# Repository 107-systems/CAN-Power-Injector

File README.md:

`CAN-Power-Injector`
====================

The purpose of this board is to inject 5V DC power at up to 5A for powering CAN bus devices.

<p align="center">
  
</p>

#### Blockdiagram

#### Electrical Parameters
| Name | Value |
|-|-|
| V_IN min | 10.5 V | set by resistor divider(R7/R8) |
| V_IN max | 40.0 V | limited by TVS diode (D4) |
| V_CAN_OUT | 5.0 V to 5.5 V|
| I_CAN_OUT,CONTINUOUS | 5.0 A |

#### Inputs
| Designator | Name | Connector |
|-|-|-|
| CN4 | Battery (4S / 4100 mAh LiFePo) | [Powerpole® PP15 to PP45](https://www.andersonpower.com/content/dam/app/ecommerce/product-pdfs/PP-Pak/ds-pp1545.pdf) |
| CN1 | Battery | 3.5 mm screw terminal (not populated) |

#### Outputs
| Designator | Name | Connector |
|-|-|-|
| CN2 and CN3 | CAN channel 1 | JST GH 1.25mm 4-pin. |
| CN5 and CN6 | CAN channel 2 | JST GH 1.25mm 4-pin. |
| CN7 | 5V | 5V output, internal for testing (not populated) |

## Enclosure

There exists a 3D printable enclosure to encapsulate the PCB.

### Standard

### Low profile

## PCB
### Top

### Bottom

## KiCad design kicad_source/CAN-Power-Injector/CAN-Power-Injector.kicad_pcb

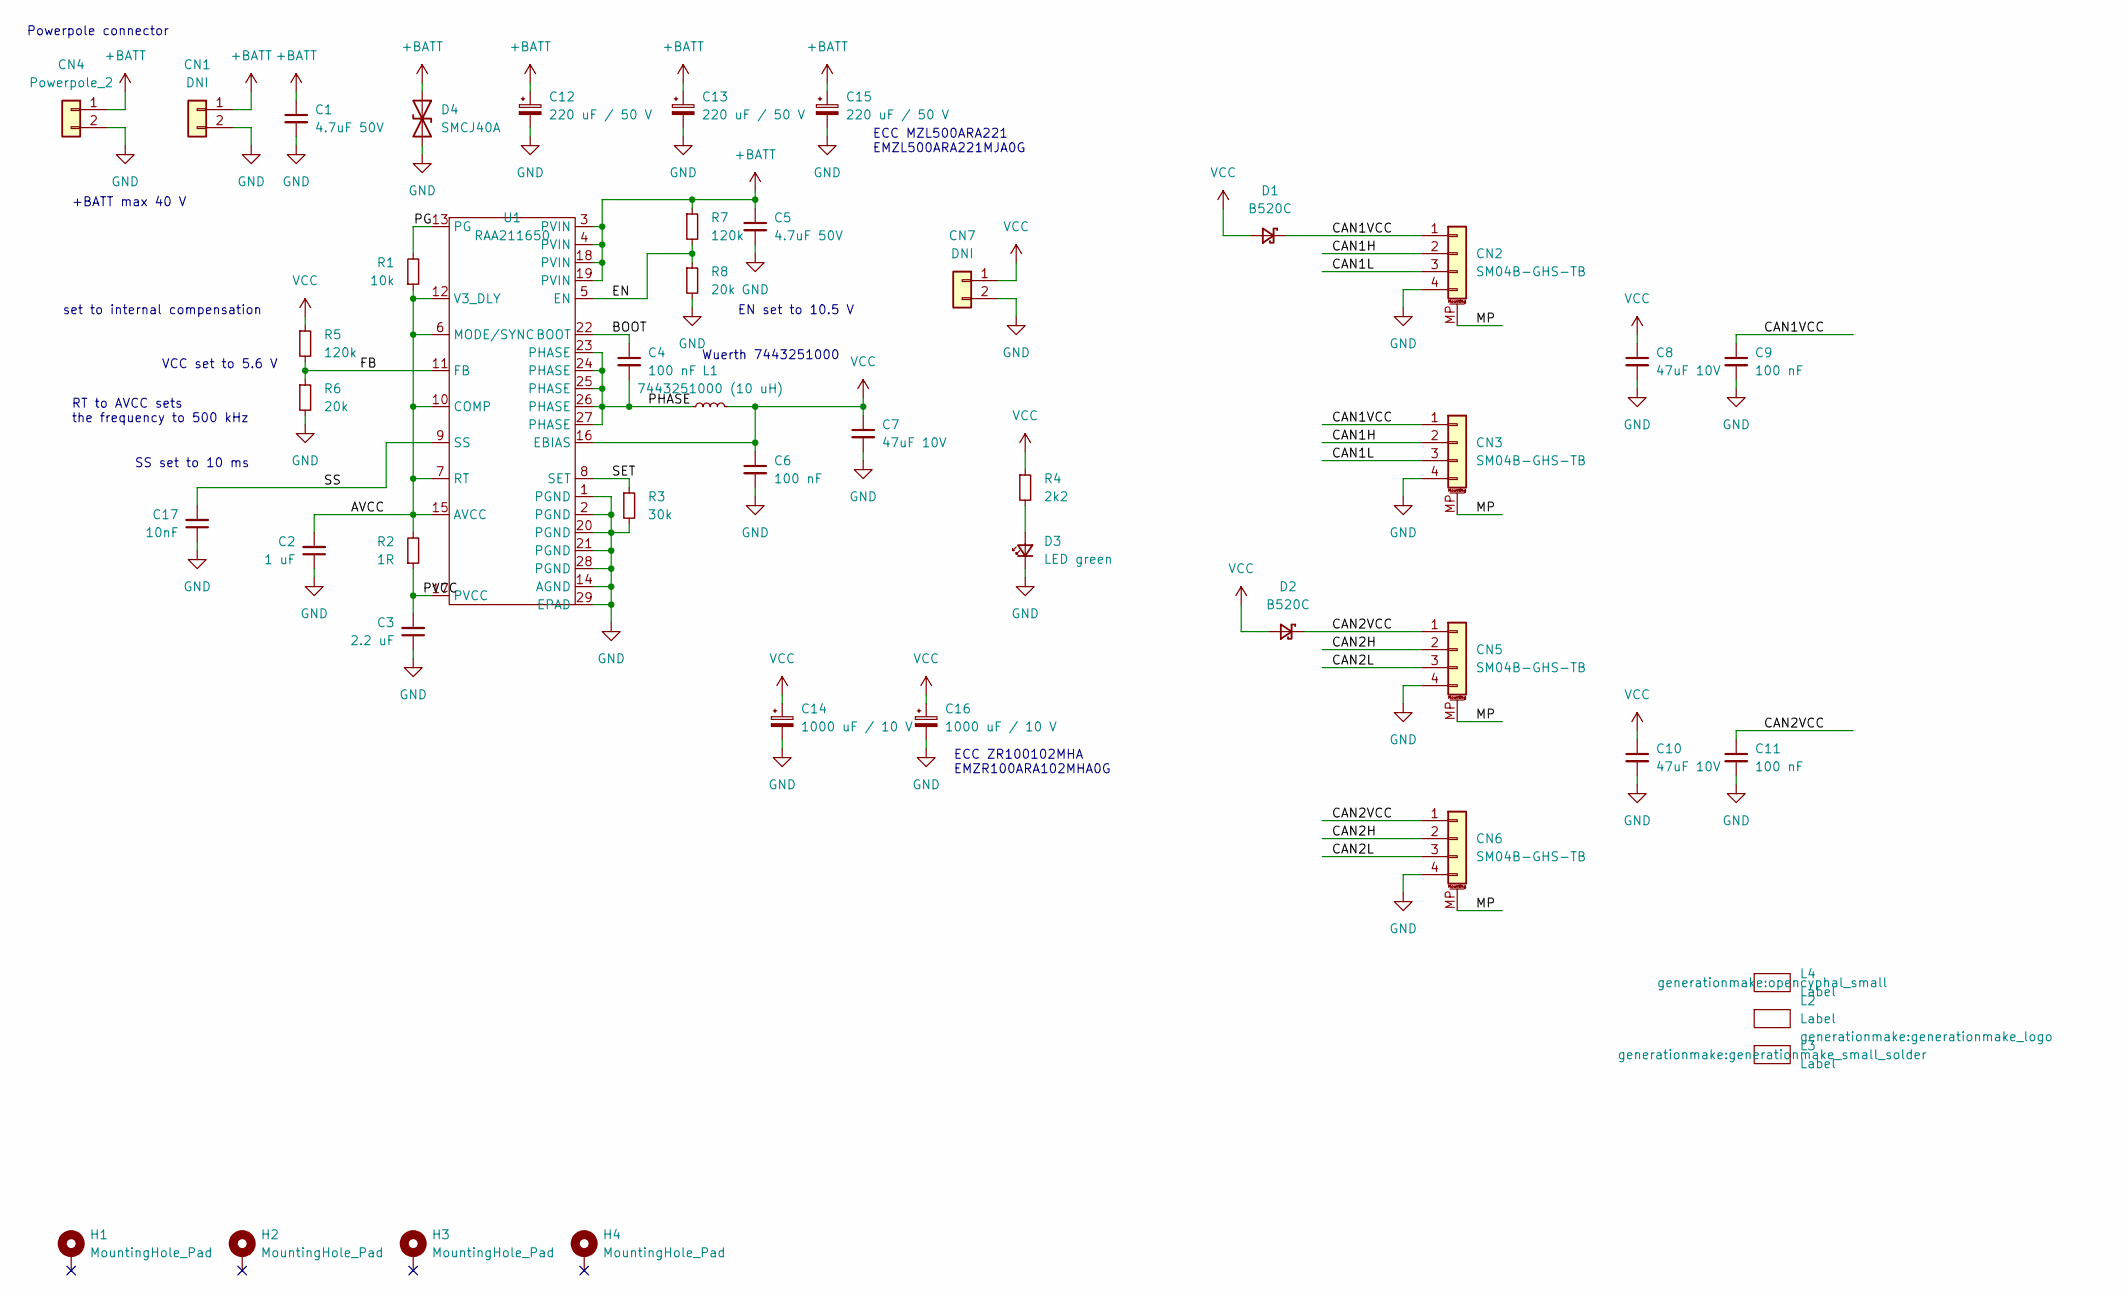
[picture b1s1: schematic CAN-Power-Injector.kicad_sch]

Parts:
C1, C5: 4.7uF 50V; C_1210_3225Metric
C2: 1 uF; C_0603_1608Metric
C3: 2.2 uF; C_0603_1608Metric
C4, C6, C9, C11: 100 nF; C_0603_1608Metric
C7, C8, C10: 47uF 10V; C_1210_3225Metric
C12, C13, C15: 220 uF / 50 V; CP_Elec_10x10
C14, C16: 1000 uF / 10 V; CP_Elec_8x10
C17: 10nF; C_0603_1608Metric
CN1: DNI; PhoenixContact_MC_1,5_2-G-3.5_1x02_P3.50mm_Horizontal
CN2, CN3, CN5, CN6: SM04B-GHS-TB; JST_GH_SM04B-GHS-TB_1x04-1MP_P1.25mm_Horizontal
CN4: Powerpole_2; POWERPOLE_hor_2
CN7: DNI; PinHeader_1x02_P2.54mm_Vertical
D1, D2: B520C; D_SMC
D3: LED green; LED_0603_1608Metric
D4: SMCJ40A; D_SMC
H1, H2, H3, H4: MountingHole_Pad; MountingHole_3.2mm_M3_DIN965_Pad
L1: 7443251000 (10 uH); L_Wuerth_HCI-1050
L2: Label; generationmake_logo
L3: Label; generationmake_small_solder
L4: Label; opencyphal_small
R1: 10k; R_0603_1608Metric
R2: 1R; R_0603_1608Metric
R3: 30k; R_0603_1608Metric
R4: 2k2; R_0603_1608Metric
R5, R7: 120k; R_0603_1608Metric
R6, R8: 20k; R_0603_1608Metric
U1: RAA211650; QFN-28-1EP_4x5mm_P0.5mm_EP2.65x3.65mm

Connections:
+BATT: C1.1, C5.1, C12.1, C13.1, C15.1, CN1.1, CN4.1, D4.1 (A1), R7.1, U1.3 (PVIN), U1.4 (PVIN), U1.18 (PVIN), U1.19 (PVIN)
/AVCC: C2.2, R1.1, R2.2, U1.6 (MODE/SYNC), U1.7 (RT), U1.10 (COMP), U1.12 (V3_DLY), U1.15 (AVCC)
/BOOT: C4.1, U1.22 (BOOT)
/CAN1H: CN2.2, CN3.2
/CAN1L: CN2.3, CN3.3
/CAN1VCC: C9.1, CN2.1, CN3.1, D1.1 (K)
/CAN2H: CN5.2, CN6.2
/CAN2L: CN5.3, CN6.3
/CAN2VCC: C11.1, CN5.1, CN6.1, D2.1 (K)
/EN: R7.2, R8.1, U1.5 (EN)
/FB: R5.2, R6.1, U1.11 (FB)
/MP: CN2.MP (MountPin), CN3.MP (MountPin), CN5.MP (MountPin), CN6.MP (MountPin)
/PG: R1.2, U1.13 (PG)
/PHASE: C4.2, L1.1, U1.23 (PHASE), U1.24 (PHASE), U1.25 (PHASE), U1.26 (PHASE), U1.27 (PHASE)
/PVCC: C3.2, R2.1, U1.17 (PVCC)
/SET: R3.1, U1.8 (SET)
/SS: C17.2, U1.9 (SS)
GND: C1.2, C2.1, C3.1, C5.2, C6.2, C7.2, C8.2, C9.2, C10.2, C11.2, C12.2, C13.2, C14.2, C15.2, C16.2, C17.1, CN1.2, CN2.4, CN3.4, CN4.2, CN5.4, CN6.4, CN7.2, D3.1 (K), D4.2 (A2), R3.2, R6.2, R8.2, U1.1 (PGND), U1.2 (PGND), U1.14 (AGND), U1.20 (PGND), U1.21 (PGND), U1.28 (PGND), U1.29 (EPAD)
unnamed: D3.2 (A), R4.2
VCC: C6.1, C7.1, C8.1, C10.1, C14.1, C16.1, CN7.1, D1.2 (A), D2.2 (A), L1.2, R4.1, R5.1, U1.16 (EBIAS)

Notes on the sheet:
Wuerth 7443251000
EN set to 10.5 V
+BATT max 40 V
ECC ZR100102MHA EMZR100ARA102MHA0G
set to internal compensation
ECC MZL500ARA221 EMZL500ARA221MJA0G
RT to AVCC sets the frequency to 500 kHz
VCC set to 5.6 V
Powerpole connector
SS set to 10 ms

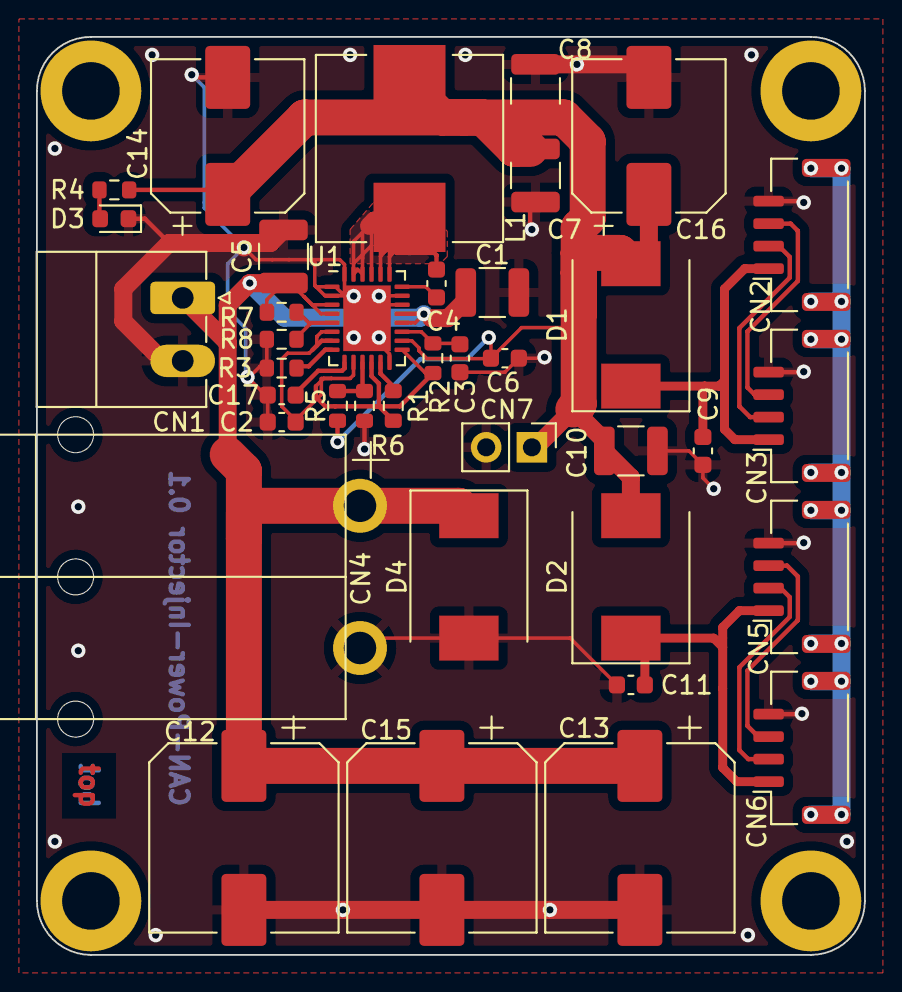
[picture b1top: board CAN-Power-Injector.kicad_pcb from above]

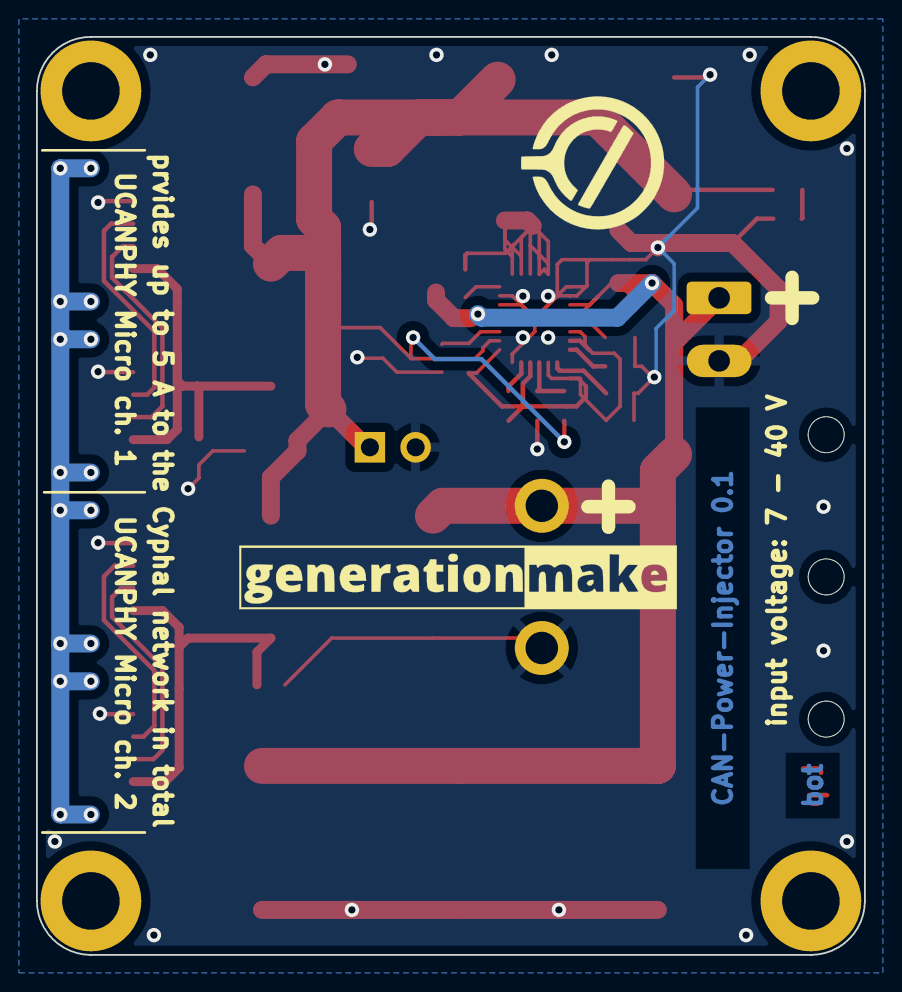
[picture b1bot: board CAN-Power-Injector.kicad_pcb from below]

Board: 2 copper layers, 46.0 x 51.0 mm, 45 parts (2 on the bottom side), 20 nets.

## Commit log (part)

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2022-07-18 Initial commit.
2022-07-18 Fix typo.
2022-07-18 Minimal specification.
2022-08-23 Add l3xz logo.
2022-08-23 Add l3xz logo. (#2)
2022-08-24 Increase logo size to 40%.
2022-10-17 Adding sync-labels workflow.
2022-10-17 Adding sync-labels workflow. (#3)
2022-10-17 enroll dependabot
2022-10-17 enroll dependabot (#4)
2022-10-17 Bump actions/upload-artifact from 2 to 3
    Bumps [actions/upload-artifact](https://github.com/actions/upload-artifact) from 2 to 3.
    - [Release notes](https://github.com/actions/upload-artifact/releases)
    - [Commits](https://github.com/actions/upload-artifact/compare/v2...v3)
    ---
    updated-dependencies:
    - dependency-name: actions/upload-artifact
2022-10-17 Bump actions/checkout from 2 to 3
    Bumps [actions/checkout](https://github.com/actions/checkout) from 2 to 3.
    - [Release notes](https://github.com/actions/checkout/releases)
    - [Changelog](https://github.com/actions/checkout/blob/main/CHANGELOG.md)
    - [Commits](https://github.com/actions/checkout/compare/v2...v3)
    ---
    updated-dependencies:
2022-10-17 Bump geekyeggo/delete-artifact from 1 to 2
    Bumps [geekyeggo/delete-artifact](https://github.com/geekyeggo/delete-artifact) from 1 to 2.
    - [Release notes](https://github.com/geekyeggo/delete-artifact/releases)
    - [Commits](https://github.com/geekyeggo/delete-artifact/compare/v1...v2)
    ---
    updated-dependencies:
    - dependency-name: geekyeggo/delete-artifact
2022-10-17 Bump actions/download-artifact from 2 to 3
    Bumps [actions/download-artifact](https://github.com/actions/download-artifact) from 2 to 3.
    - [Release notes](https://github.com/actions/download-artifact/releases)
    - [Commits](https://github.com/actions/download-artifact/compare/v2...v3)
    ---
    updated-dependencies:
    - dependency-name: actions/download-artifact
2022-10-17 Bump carlosperate/download-file-action from 1.0.3 to 1.1.1
    Bumps [carlosperate/download-file-action](https://github.com/carlosperate/download-file-action) from 1.0.3 to 1.1.1.
    - [Release notes](https://github.com/carlosperate/download-file-action/releases)
    - [Commits](https://github.com/carlosperate/download-file-action/compare/v1.0.3...v1.1.1)
    ---
    updated-dependencies:
    - dependency-name: carlosperate/download-file-action
2022-10-17 Bump carlosperate/download-file-action from 1.0.3 to 1.1.1 (#9)
    Bumps [carlosperate/download-file-action](https://github.com/carlosperate/download-file-action) from 1.0.3 to 1.1.1.
    - [Release notes](https://github.com/carlosperate/download-file-action/releases)
    - [Commits](https://github.com/carlosperate/download-file-action/compare/v1.0.3...v1.1.1)
    ---
    updated-dependencies:
    - dependency-name: carlosperate/download-file-action
2022-10-17 Bump actions/download-artifact from 2 to 3 (#8)
    Bumps [actions/download-artifact](https://github.com/actions/download-artifact) from 2 to 3.
    - [Release notes](https://github.com/actions/download-artifact/releases)
    - [Commits](https://github.com/actions/download-artifact/compare/v2...v3)
    ---
    updated-dependencies:
    - dependency-name: actions/download-artifact
2022-10-17 Bump actions/checkout from 2 to 3 (#6)
    Bumps [actions/checkout](https://github.com/actions/checkout) from 2 to 3.
    - [Release notes](https://github.com/actions/checkout/releases)
    - [Changelog](https://github.com/actions/checkout/blob/main/CHANGELOG.md)
    - [Commits](https://github.com/actions/checkout/compare/v2...v3)
    ---
    updated-dependencies:
2022-10-17 Bump actions/upload-artifact from 2 to 3 (#5)
    Bumps [actions/upload-artifact](https://github.com/actions/upload-artifact) from 2 to 3.
    - [Release notes](https://github.com/actions/upload-artifact/releases)
    - [Commits](https://github.com/actions/upload-artifact/compare/v2...v3)
    ---
    updated-dependencies:
    - dependency-name: actions/upload-artifact
2022-10-23 added kicad project
2022-10-24 added switching regulator to schematic
2022-10-24 updated and annotated schematic
2022-10-24 started layout
2022-10-24 added images of pcb
2022-10-24 Bump carlosperate/download-file-action from 1.1.1 to 2.0.0
    Bumps [carlosperate/download-file-action](https://github.com/carlosperate/download-file-action) from 1.1.1 to 2.0.0.
    - [Release notes](https://github.com/carlosperate/download-file-action/releases)
    - [Commits](https://github.com/carlosperate/download-file-action/compare/v1.1.1...v2.0.0)
    ---
    updated-dependencies:
    - dependency-name: carlosperate/download-file-action
2022-10-24 Bump carlosperate/download-file-action from 1.1.1 to 2.0.0 (#10)
    Bumps [carlosperate/download-file-action](https://github.com/carlosperate/download-file-action) from 1.1.1 to 2.0.0.
    - [Release notes](https://github.com/carlosperate/download-file-action/releases)
    - [Commits](https://github.com/carlosperate/download-file-action/compare/v1.1.1...v2.0.0)
    ---
    updated-dependencies:
    - dependency-name: carlosperate/download-file-action
2022-10-25 added Powerpole connector
2022-10-30 addedhoricontal powerpole
2022-10-31 added second uavcan channel and diodes
2022-10-31 added LED
2022-10-31 added TVS diode and capacitors, updated layout
2022-11-04 changed connector for input, added connector for VCC
2022-11-05 updated and set analog values of switching regulator
2022-11-06 updated some component values
2022-11-06 made drc, corrected some errors, added label
2022-11-07 updated schematic pdf and images
2022-11-07 Fixing table (layout error, also dropping old vbat specification)
2022-11-30 added some texts to pcb, generated BOM, updated schemtatic pdf
2022-12-12 added some labels
2023-01-06 added step file of pcb
2023-01-06 added freecad project with enclosure
2023-01-06 added production data with stl files
2023-01-06 added image of enclosure
2023-01-06 made design transparent
2023-01-08 increased enclosure height by 3 mm, added hex holes on bottom
2023-01-08 improved spacer
2023-01-08 updated image and production data
2023-01-20 increased hole size
2023-01-20 designed low profile enclosure
2023-01-20 added image of low profile enclosure
2023-01-21 increased hole size for capacitors by 1 mm, added blocking wall near the can connectors
2023-01-22 add prusa slicer project
2023-01-24 Update production data.
2023-01-24 Rename all files to CAN-Power-Injector.
2023-01-24 Reduce size of images for better readability.
2023-02-16 License under CERN Open Hardware Licence Version 2.
2023-02-16 License under CERN Open Hardware Licence Version 2. (#16)
2023-02-16 Add CI workflow to check for commonly misspelled words
    On every push, pull request, and periodically, use codespell to check for commonly
    misspelled words.
    In the event of a false positive, the problematic word should be added, in all lowercase, to the
    field of . Regardless of the case of the word in the false positive, it must be in all lowercase in the
    ignore list. The ignore list is comma-separated with no spaces.
2023-02-16 Ignore STEP files.
2023-02-16 Fix spelling mistakes.!
2023-02-16 Adding CI spell check badge.
2023-02-16 Adding CI spell check badge. (#18)
2023-05-01 changed R5 to 110 k. this changes VCC to 5.2V
2023-05-01 increased C17 to 33 nF to achieve a soft start of 5.28 ms because of high output capacitance
2023-05-01 updated schematic pdf
2023-08-09 Bump carlosperate/download-file-action from 2.0.0 to 2.0.1
    Bumps [carlosperate/download-file-action](https://github.com/carlosperate/download-file-action) from 2.0.0 to 2.0.1.
    - [Release notes](https://github.com/carlosperate/download-file-action/releases)
    - [Commits](https://github.com/carlosperate/download-file-action/compare/v2.0.0...v2.0.1)
    ---
    updated-dependencies:
    - dependency-name: carlosperate/download-file-action
2023-09-04 Bump actions/checkout from 3 to 4
    Bumps [actions/checkout](https://github.com/actions/checkout) from 3 to 4.
    - [Release notes](https://github.com/actions/checkout/releases)
    - [Changelog](https://github.com/actions/checkout/blob/main/CHANGELOG.md)
    - [Commits](https://github.com/actions/checkout/compare/v3...v4)
    ---
    updated-dependencies:
2023-09-04 Bump actions/checkout from 3 to 4 (#21)
    Bumps [actions/checkout](https://github.com/actions/checkout) from 3 to 4.
    - [Release notes](https://github.com/actions/checkout/releases)
    - [Changelog](https://github.com/actions/checkout/blob/main/CHANGELOG.md)
    - [Commits](https://github.com/actions/checkout/compare/v3...v4)
    ---
    updated-dependencies:
2023-12-15 Bump actions/upload-artifact from 3 to 4
    Bumps [actions/upload-artifact](https://github.com/actions/upload-artifact) from 3 to 4.
    - [Release notes](https://github.com/actions/upload-artifact/releases)
    - [Commits](https://github.com/actions/upload-artifact/compare/v3...v4)
    ---
    updated-dependencies:
    - dependency-name: actions/upload-artifact
2023-12-15 Bump actions/download-artifact from 3 to 4
    Bumps [actions/download-artifact](https://github.com/actions/download-artifact) from 3 to 4.
    - [Release notes](https://github.com/actions/download-artifact/releases)
    - [Commits](https://github.com/actions/download-artifact/compare/v3...v4)
    ---
    updated-dependencies:
    - dependency-name: actions/download-artifact
2023-12-15 Bump actions/download-artifact from 3 to 4 (#24)
    Bumps [actions/download-artifact](https://github.com/actions/download-artifact) from 3 to 4.
    - [Release notes](https://github.com/actions/download-artifact/releases)
    - [Commits](https://github.com/actions/download-artifact/compare/v3...v4)
    ---
    updated-dependencies:
    - dependency-name: actions/download-artifact
2023-12-15 Bump actions/upload-artifact from 3 to 4 (#23)
    Bumps [actions/upload-artifact](https://github.com/actions/upload-artifact) from 3 to 4.
    - [Release notes](https://github.com/actions/upload-artifact/releases)
    - [Commits](https://github.com/actions/upload-artifact/compare/v3...v4)
    ---
    updated-dependencies:
    - dependency-name: actions/upload-artifact
2023-12-25 Bump geekyeggo/delete-artifact from 2 to 4
    Bumps [geekyeggo/delete-artifact](https://github.com/geekyeggo/delete-artifact) from 2 to 4.
    - [Release notes](https://github.com/geekyeggo/delete-artifact/releases)
    - [Changelog](https://github.com/GeekyEggo/delete-artifact/blob/main/CHANGELOG.md)
    - [Commits](https://github.com/geekyeggo/delete-artifact/compare/v2...v4)
    ---
    updated-dependencies:
2023-12-25 Bump geekyeggo/delete-artifact from 2 to 4 (#25)
    Bumps [geekyeggo/delete-artifact](https://github.com/geekyeggo/delete-artifact) from 2 to 4.
    - [Release notes](https://github.com/geekyeggo/delete-artifact/releases)
    - [Changelog](https://github.com/GeekyEggo/delete-artifact/blob/main/CHANGELOG.md)
    - [Commits](https://github.com/geekyeggo/delete-artifact/compare/v2...v4)
    ---
    updated-dependencies:
2024-03-19 Bump geekyeggo/delete-artifact from 4 to 5
    Bumps [geekyeggo/delete-artifact](https://github.com/geekyeggo/delete-artifact) from 4 to 5.
    - [Release notes](https://github.com/geekyeggo/delete-artifact/releases)
    - [Changelog](https://github.com/GeekyEggo/delete-artifact/blob/main/CHANGELOG.md)
    - [Commits](https://github.com/geekyeggo/delete-artifact/compare/v4...v5)
    ---
    updated-dependencies:
